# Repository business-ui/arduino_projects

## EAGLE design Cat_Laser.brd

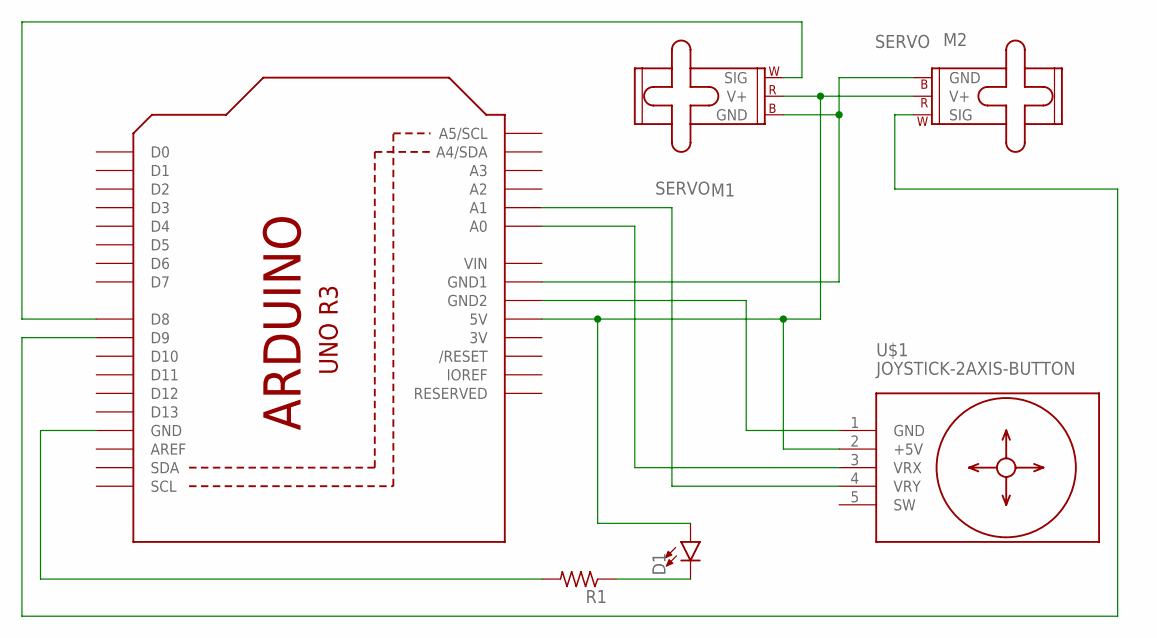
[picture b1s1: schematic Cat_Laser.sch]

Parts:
D1: LED3MM; LED_3MM
M1, M2: SERVO; 1X03
R1: FLIPFLOP-RES; 0805-THM
U1: ARDUINOR3-BPLACE
U$1: JOYSTICK-2AXIS-BUTTON

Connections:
3V: U1.3V
unnamed: M1.3 (GND), M2.3 (GND), U1.GND1
unnamed: U1.GND2, U$1.1 (GND)
unnamed: D1.A, M1.2 (V+), M2.2 (V+), U1.5V, U$1.2 (+5V)
unnamed: U1.A0, U$1.3 (VRX)
unnamed: U1.A1, U$1.4 (VRY)
unnamed: M1.1 (SIG), U1.D8
unnamed: M2.1 (SIG), U1.D9
unnamed: R1.2, U1.GND
unnamed: D1.K (C), R1.1
VIN: U1.VIN

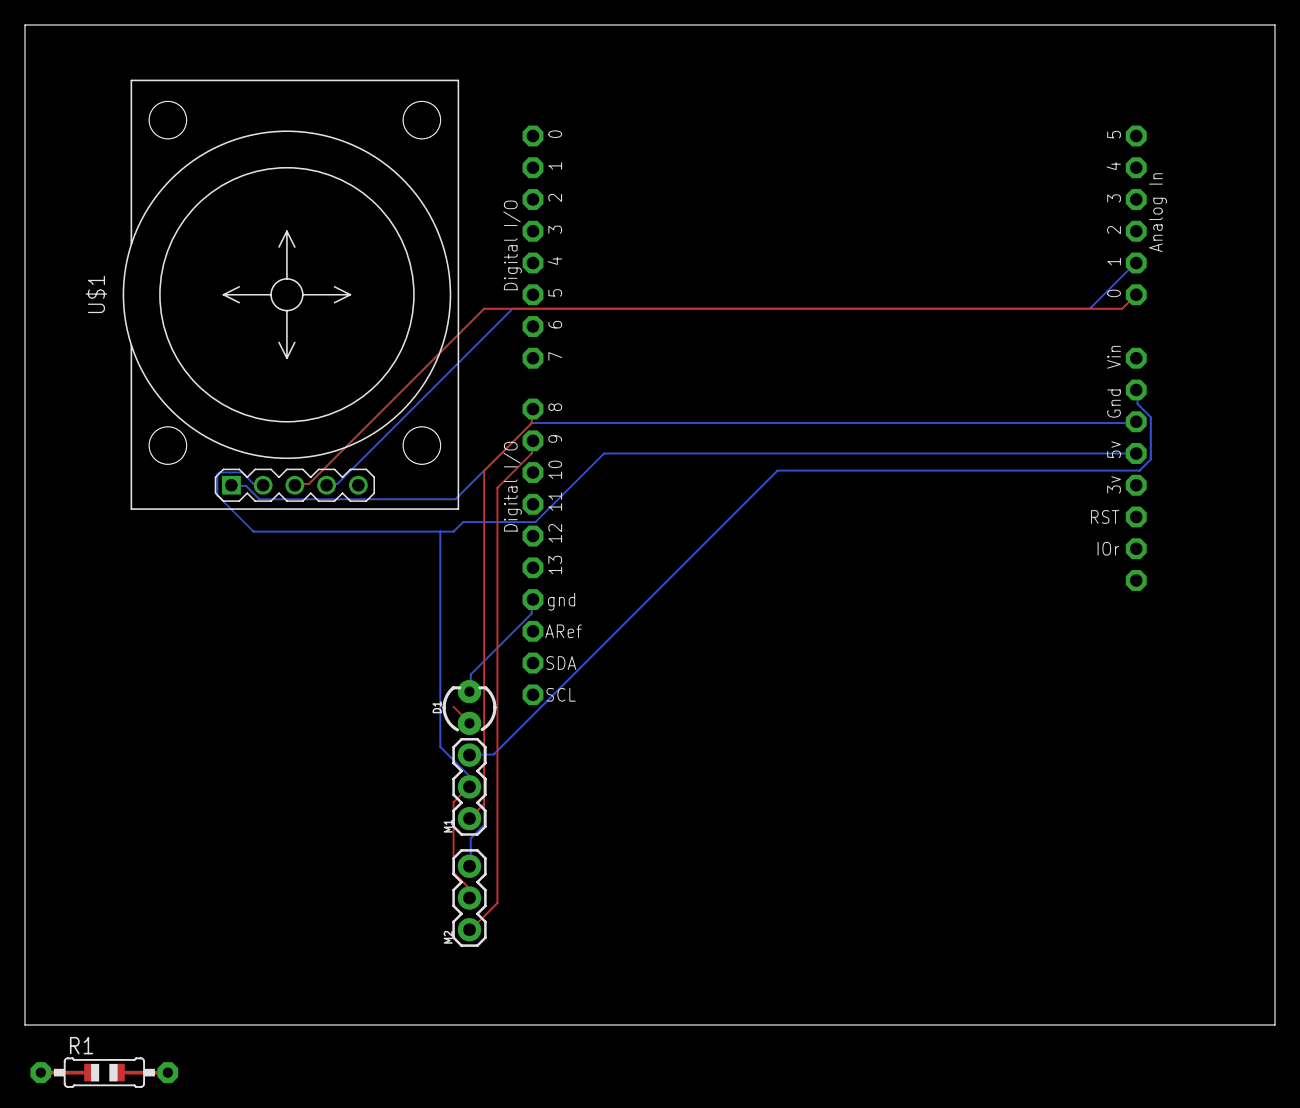
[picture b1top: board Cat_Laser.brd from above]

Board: 2 copper layers, 100.0 x 80.0 mm, 6 parts (0 on the bottom side), 9 nets.

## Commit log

2019-10-08 Add Joystick Laser Project Code
2019-10-08 Add Tinkercad Circuit Design Link to comments
2019-12-21 Added the Schematic, Board, and basic 3D Rendering
    A working simulation of the circuit design I made with Tinkercad:
    https://www.tinkercad.com/things/lQk9Ut7yoke-joysticklaser

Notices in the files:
parts and their libraries:
SparkFun-LED: Licensing: Creative Commons ShareAlike 4.0 International - https://creativecommons.org/licenses/by-sa/4.0
diy-modules: Released under the Creative Commons Attribution 4.0 International License: http://creativecommons.org/licenses/by/4.0
